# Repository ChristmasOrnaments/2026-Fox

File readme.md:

Christmas ornament number 14...

***

The detailed explanation of the original Snowman ornament is [here](https://github.com/timtilities/ChristmasOrnaments--2013-Snowman).

This ornament has been redesigned around the newer Attiny412. The schematic and PCB have been updated to use UPDI programming and the new pinout of the Attiny412. Since these use UPDI, you will need a programmer. I am currently using a [converted Arduino Nano](https://daumemo.com/diy-updi-usb-programmer-which-can-be-made-with-cheap-hardware/) as a [jtag2updi](https://github.com/ElTangas/jtag2updi) programmer. 

### Compiling with Arduino IDE

* Install [megaTinyCore](https://github.com/SpenceKonde/megaTinyCore) using the boards manager
* Select **Attiny412/402/212/202** from the boards list
* Set the *Clock source* to **4MHz (internal)**
* Set *B.O.D Mode* to **Disabled**
* Set *B.O.D. voltage level* to **1.8v**
* Select the **Attiny412** chip
* Select **Burn Bootloader** to write the fuses
* Compile and upload the program to the MCU

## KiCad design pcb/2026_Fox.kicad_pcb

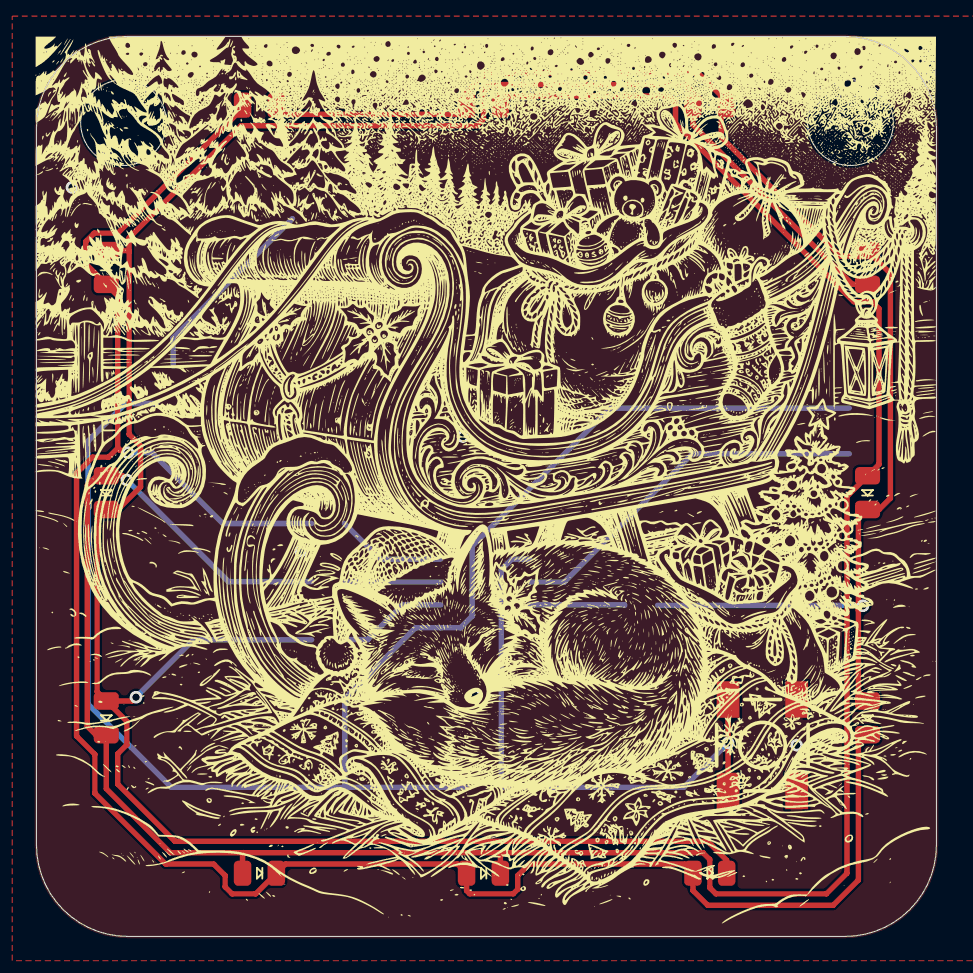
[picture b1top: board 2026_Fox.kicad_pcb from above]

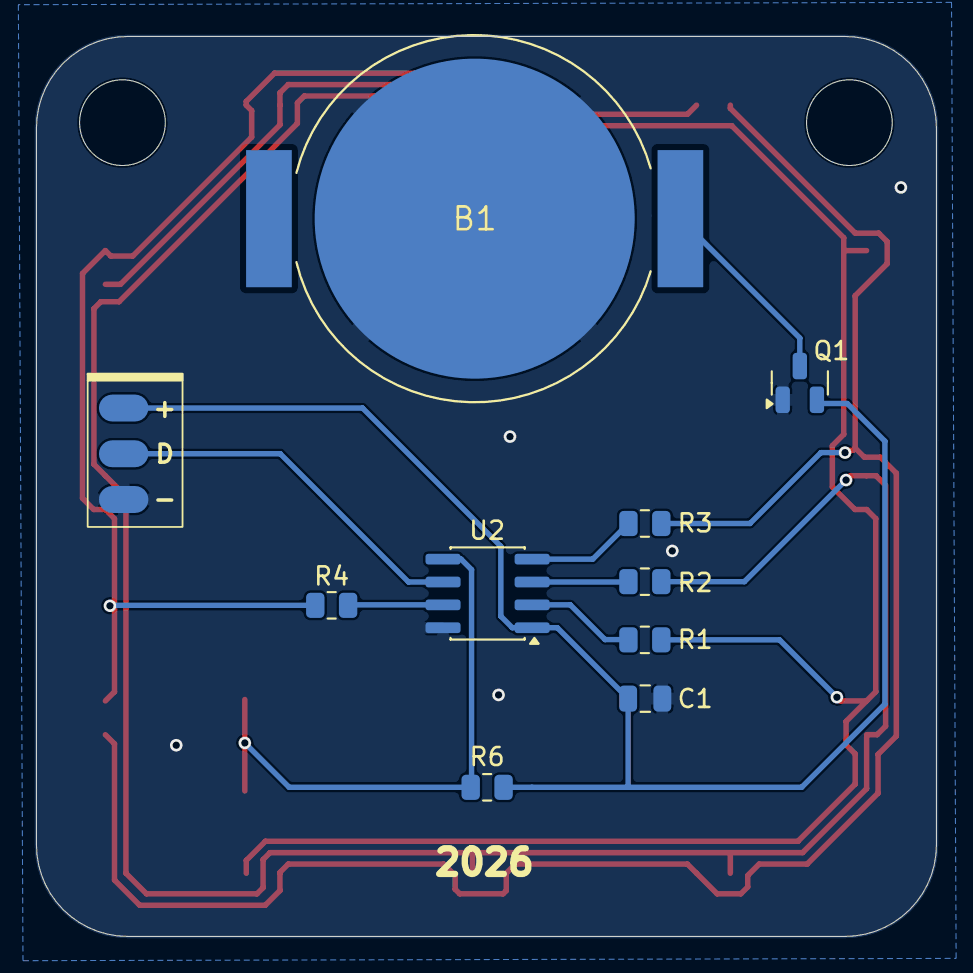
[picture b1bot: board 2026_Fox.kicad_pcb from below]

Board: 2 copper layers, 50.0 x 50.0 mm, 25 parts (10 on the bottom side), 13 nets.

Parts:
B1: CR2032; BAT-HLD-001
C1: 0.1uF; C_0805_2012Metric
D1, D5, D8, D12: RED; LED_0805_2012Metric_Red
D2, D4, D9, D10: WHITE; LED_0805_2012Metric_White
D3, D6, D7, D11: GREEN; LED_0805_2012Metric_Green
J1: UPDI; AVR_UPDI_3_SMD
Q1: DMG2305UX; SOT-23
R1, R2, R3, R4: 39; R_0805_2012Metric
R6: 10k; R_0805_2012Metric
S1: TACTILE_SWITCH_SMD
TH*: NPTH
TH*#2: NPTH
U2: ATtiny412-SS; SOIC-8_3.9x4.9mm_P1.27mm

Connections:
+VCC: C1.1, J1.1 (Vcc), Q1.2 (S), R6.1, U2.1 (VCC)
/BUTTON: R6.2, S1.3, S1.4, U2.5 (PA2)
/D0/PA6: R1.2, U2.2 (PA6)
/D1/PA7: R2.2, U2.3 (PA7)
/D2/PA1: R3.2, U2.4 (PA1)
/D4/PA3: R4.2, U2.7 (PA3)
/UPDI: J1.2 (UPDI), U2.6 (~RESET/PA0)
GND: B1.-, C1.2, J1.3 (Gnd), Q1.1 (G), S1.1, S1.2, U2.8 (GND)
unnamed: D1.2 (A), D2.1 (K), D7.2 (A), D8.1 (K), D11.2 (A), D12.1 (K), R1.1
unnamed: D1.1 (K), D2.2 (A), D3.2 (A), D4.1 (K), D9.2 (A), D10.1 (K), R2.1
unnamed: D3.1 (K), D4.2 (A), D5.2 (A), D6.1 (K), D7.1 (K), D8.2 (A), R3.1
unnamed: D5.1 (K), D6.2 (A), D9.1 (K), D10.2 (A), D11.1 (K), D12.2 (A), R4.1
unnamed: B1.+@1, B1.+@2, Q1.3 (D)

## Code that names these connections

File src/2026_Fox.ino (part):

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/* ATTINY412 / ARDUINO
 *                      ____
 *               VCC  1|*   |8  GND
 *         (D0)  PA6  2|    |7  PA3  (D4)
 *         (D1)  PA7  3|    |6  PA0  (D5)  UPDI
 *    PWM  (D2)  PA1  4|____|5  PA2  (D3)  PWM
 */

#include <avr/sleep.h>

#define DISPLAY_SEQUENCE(seq, speed) displaySequence(seq, sizeof(seq) / sizeof(seq[0]), speed)

constexpr uint8_t ButtonPin = PIN_PA2; // D3 - Pullup on the PCB (disable internal pullups)
constexpr uint8_t LED_COUNT = 12; // Total number of LEDs on the PCB
constexpr uint8_t BlinkDelay = 120; // microseconds the LED will be on, then off. It can affect brightness, but mostly affects speed
constexpr uint8_t SequenceCnt = 8; // Total number of sequences to display
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// LED pin connections => { Anode, Cathode }
//   These are NOT Arduino pin numbers (D1/D2/etc)! They are **PORTA bit positions**
//   These numbers correspond to the # after 'PA' in the pinout diagram above (for MegaTinyCore).
// PA6=6 (D0), PA7=7 (D1), PA1=1 (D2), PA2=2 (D3), PA3=3 (D4), PA0=0 (D5/UPDI)
constexpr uint8_t LEDConnections[LED_COUNT][2] = {  
  { 6 , 7 }, // LED1  (PA6/D0, PA7/D1)
  { 7 , 1 }, // LED3  (PA7/D1, PA1/D2)
  { 1 , 3 }, // LED5  (PA1/D2, PA3/D4)
  { 7 , 6 }, // LED2  (PA7/D1, PA6/D0)
  { 1 , 7 }, // LED4  (PA1/D2, PA7/D1)
  { 3 , 1 }, // LED6  (PA3/D4, PA1/D2)
  { 6 , 1 }, // LED7  (PA6/D0, PA1/D2)
  { 7 , 3 }, // LED9  (PA7/D1, PA3/D4)
  { 1 , 6 }, // LED8  (PA1/D2, PA6/D0)
  { 3 , 7 }, // LED10 (PA3/D4, PA7/D1)
  { 6 , 3 }, // LED11 (PA6/D0, PA3/D4)
  { 3 , 6 }  // LED12 (PA3/D4, PA6/D0)
};

/**************************************************************************/
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// Button (Execute) ISR
ISR(PORTA_PORT_vect) {
    //PORTA.INTFLAGS = 0xFF; // Clear all Port A flags
    PORTA.INTFLAGS = PORT_INT2_bm; // Clear PA2 interrupt flag
    TriggerNow = true;
}

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    PORTA.PIN7CTRL = PORT_ISC_INPUT_DISABLE_gc;
    // Enable the input buffer for ButtonPin
    *(&PORTA.PIN0CTRL + digitalPinToBitPosition(ButtonPin)) = PORT_ISC_FALLING_gc;
    // If I set ButtonPin to the bit position (2) instead of PIN_PA2, I wouldn't need digitalPinToBitPosition(), but it would be more confusing
}

// Initialize the 32KHz internal ultra low power 32 kHz oscillator 
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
